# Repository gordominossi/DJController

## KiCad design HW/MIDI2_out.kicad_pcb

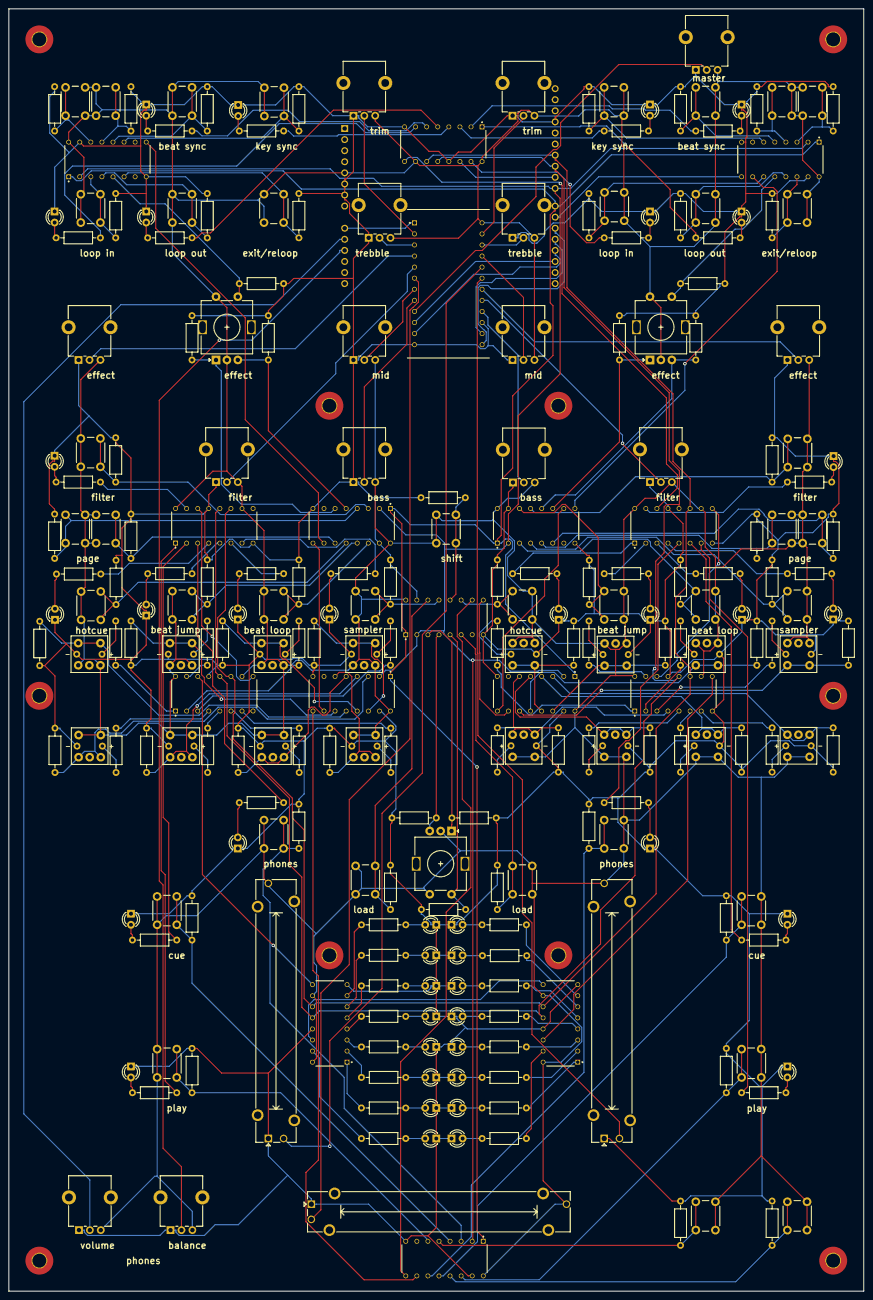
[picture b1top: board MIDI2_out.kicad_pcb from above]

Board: 2 copper layers, 196.0 x 294.0 mm, 263 parts (1 on the bottom side), 220 nets.

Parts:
A1: Arduino_UNO_R3
B0, B1, B2, B3, B4, B5, B6, B7: 74HC165; DIP794W45P254L1969H508Q16
D1, D2, D3, D4, D5, D6, D7, D8, D9, D10, D11, D12, D13, D14, D15, D16, D25, D26, D27, D28, D29, D30, D31, D32, D41, D42, D43, D44, D45, D46, D47, D48, D49, D50, D51, D52, D53, D54, D55, D56: LED; LED_D3.0mm
H0, H1, H2, H3, H4, H5, H6, H7, H8, H9: MountingHole_3.2mm_M3_Pad_TopBottom
L0, L1, L2, L3, L4, L5, L6: 74AHC595; DIP794W45P254L1969H508Q16
M0: CD74HC4067M; DIP1549W45P254L3404H940Q24
R1, R2, R3, R4, R5, R6, R7, R8, R9, R10, R11, R12, R13, R14, R15, R16, R17, R18, R19, R20, R21, R22, R23, R24, R25, R26, R27, R28, R29, R30, R31, R32, R33, R34, R35, R36, R37, R38, R39, R40, R41, R42, R43, R44, R45, R46, R47, R48, R49, R50, R51, R52, R53, R54, R55, R56: 220; R_Axial_DIN0207_L6.3mm_D2.5mm_P10.16mm_Horizontal
R57, R58, R59, R60, R61, R62, R63, R64, R65, R66, R67, R68, R69, R70, R71, R72, R89, R90, R91, R93, R95, R96, R97, R98, R100, R102, R103, R105, R107, R108, R109, R110, R111, R113, R115, R116, R118, R119, R121, R122, R123, R124, R125, R126, R127, R128, R129, R131, R133, R134, R135, R136, R138, R140, R141, R142, R143, R144, R145, R146, R148, R149, R151, R152: 10k; R_Axial_DIN0207_L6.3mm_D2.5mm_P10.16mm_Horizontal
RV1, RV2, RV3, RV4, RV5, RV6, RV10, RV11, RV12, RV13, RV14, RV15, RV16, RV17, RV18: 10k; Potentiometer_Alpha_RD901F-40-00D_Single_Vertical_CircularH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
RV7, RV8, RV9: 10k; Potentiometer_Bourns_PTA4543_Single_Slide
SW1, SW2, SW4, SW5, SW7, SW9, SW11, SW12, SW14, SW15, SW19, SW21, SW22, SW23, SW24, SW26, SW27, SW29, SW30, SW31, SW33, SW34, SW36, SW37, SW38, SW40, SW41, SW43, SW44, SW45, SW46, SW47, SW49, SW50, SW52, SW53, SW54, SW56, SW57: SW_Push; SW_PUSH_6mm_H13mm
SW3, SW6, SW10, SW13, SW17, SW20, SW25, SW28, SW32, SW35, SW39, SW42, SW48, SW51, SW55, SW58: SW_SPST_LED_2; TS5
SW8, SW16, SW18: Rotary_Encoder_Switch; RotaryEncoder_Alps_EC11E-Switch_Vertical_H20mm

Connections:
+5V: A1.5, B0.16, B1.16, B2.16, B3.16, B4.16, B5.16, B6.16, B7.16, L0.10, L0.16, L1.10, L1.16, L2.10, L2.16, L3.10, L3.16, L4.10, L4.16, L5.10, L5.16, L6.10, L6.16, M0.24, RV1.3, RV2.3, RV3.3, RV4.3, RV5.3, RV6.3, RV7.3, RV8.3, RV9.3, RV10.3, RV11.3, RV12.3, RV13.3, RV14.3, RV15.3, RV16.3, RV17.3, RV18.3, SW1.2, SW2.2, SW3.1, SW3.2, SW4.2, SW5.1, SW6.1, SW6.2, SW7.2, SW8.C, SW8.S1, SW9.2, SW10.1, SW10.2, SW11.2, SW12.1, SW13.1, SW13.2, SW14.2, SW15.2, SW16.C, SW16.S2, SW17.3, SW17.4, SW18.C, SW18.S2, SW19.1, SW20.3, SW20.4, SW21.2, SW22.2, SW23.2, SW24.2, SW25.3, SW25.4, SW26.2, SW27.1, SW28.3, SW28.4, SW29.2, SW30.2, SW31.2, SW32.1, SW32.2, SW33.1, SW34.1, SW35.1, SW35.2, SW36.1, SW37.2, SW38.2, SW39.1, SW39.2, SW40.1, SW41.1, SW42.1, SW42.2, SW43.2, SW44.2, SW45.2, SW46.2, SW47.2, SW48.3, SW48.4, SW49.1, SW50.1, SW51.3, SW51.4, SW52.2, SW53.1, SW54.2, SW55.3, SW55.4, SW56.1, SW57.1, SW58.3, SW58.4
GND: A1.6, A1.7, A1.29, B0.8, B0.15, B1.8, B1.15, B2.8, B2.15, B3.8, B3.15, B4.8, B4.15, B5.8, B5.15, B6.8, B6.15, B7.8, B7.15, D1.1, D2.1, D3.1, D4.1, D5.1, D6.1, D7.1, D8.1, D9.1, D10.1, D11.1, D12.1, D13.1, D14.1, D15.1, D16.1, D25.1, D26.1, D27.1, D28.1, D29.1, D30.1, D31.1, D32.1, D41.1, D42.1, D43.1, D44.1, D45.1, D46.1, D47.1, D48.1, D49.1, D50.1, D51.1, D52.1, D53.1, D54.1, D55.1, D56.1, L0.8, L0.13, L1.8, L1.13, L2.8, L2.13, L3.8, L3.13, L4.8, L4.13, L5.8, L5.13, L6.8, L6.13, M0.12, M0.15, R57.2, R58.2, R59.2, R60.2, R61.2, R62.2, R63.2, R64.2, R65.2, R66.2, R67.2, R68.2, R69.2, R70.2, R71.2, R72.2, R89.2, R90.2, R91.2, R93.2, R95.2, R96.2, R97.2, R98.2, R100.2, R102.2, R103.2, R105.2, R107.2, R108.2, R109.2, R110.2, R111.2, R113.2, R115.2, R116.2, R118.2, R119.2, R121.2, R122.2, R123.2, R124.2, R125.2, R126.2, R127.2, R128.2, R129.2, R131.2, R133.2, R134.2, R135.2, R136.2, R138.2, R140.2, R141.2, R142.2, R143.2, R144.2, R145.2, R146.2, R148.2, R149.2, R151.2, R152.2, RV1.1, RV2.1, RV3.1, RV4.1, RV5.1, RV6.1, RV7.1, RV8.1, RV9.1, RV10.1, RV11.1, RV12.1, RV13.1, RV14.1, RV15.1, RV16.1, RV17.1, RV18.1, SW3.5, SW6.5, SW10.5, SW13.5, SW17.5, SW20.5, SW25.5, SW28.5, SW32.5, SW35.5, SW39.5, SW42.5, SW48.5, SW51.5, SW55.5, SW58.5
unnamed: A1.9, M0.1
unnamed: A1.10, RV17.2
unnamed: A1.11, RV18.2
unnamed: A1.17, M0.10
unnamed: A1.18, M0.11
unnamed: A1.19, M0.14
unnamed: A1.20, M0.13
unnamed: A1.21, B0.9
unnamed: A1.22, B0.1, B1.1, B2.1, B3.1, B4.1, B5.1, B6.1, B7.1
unnamed: A1.23, B0.2, B1.2, B2.2, B3.2, B4.2, B5.2, B6.2, B7.2
unnamed: A1.24, L0.14
unnamed: A1.25, L0.12, L1.12, L2.12, L3.12, L4.12, L5.12, L6.12
unnamed: A1.26, L0.11, L1.11, L2.11, L3.11, L4.11, L5.11, L6.11
unnamed: B0.3, R109.1, SW9.1
unnamed: B0.4, R96.1, SW1.1
unnamed: B0.5, R140.1, SW38.1
unnamed: B0.6, R122.1, SW21.1
unnamed: B0.10, B1.9
unnamed: B0.11, R144.1, SW36.2
unnamed: B0.12, R116.1, SW16.S1
unnamed: B0.13, R136.1, SW37.1
unnamed: B0.14, R126.1, SW26.1
unnamed: B1.3, R110.1, SW11.1
unnamed: B1.4, R97.1, SW2.1
unnamed: B1.5, R143.1, SW44.1
unnamed: B1.6, R123.1, SW22.1
unnamed: B1.10, B2.9
unnamed: B1.11, R90.1, SW16.A
unnamed: B1.12, R89.1, SW16.B
unnamed: B1.13, R133.1, SW43.1
unnamed: B1.14, R127.1, SW29.1
unnamed: B2.3, R63.1, SW28.1, SW28.2
unnamed: B2.4, R61.1, SW25.1, SW25.2
unnamed: B2.5, R59.1, SW20.1, SW20.2
unnamed: B2.6, R57.1, SW17.1, SW17.2
unnamed: B2.10, B3.9
unnamed: B2.11, R71.1, SW13.3, SW13.4
unnamed: B2.12, R69.1, SW10.3, SW10.4
unnamed: B2.13, R67.1, SW6.3, SW6.4
unnamed: B2.14, R65.1, SW3.3, SW3.4
unnamed: B3.3, R107.1, SW8.A
unnamed: B3.4, R103.1, SW8.B
unnamed: B3.5, R91.1, SW8.S2
unnamed: B3.6, R148.1, SW54.1
unnamed: B3.10, B4.9
unnamed: B3.11, R135.1, SW56.2
unnamed: B3.12, R134.1, SW49.2
unnamed: B3.13, R128.1, SW40.2
unnamed: B3.14, R118.1, SW33.2
unnamed: B4.3, R113.1, SW27.2
unnamed: B4.4, R105.1, SW19.2
unnamed: B4.5, R100.1, SW12.2
unnamed: B4.6, R93.1, SW5.2
unnamed: B4.10, B5.9
unnamed: B4.11, R149.1, SW57.2
unnamed: B4.12, R138.1, SW50.2
unnamed: B4.13, R131.1, SW41.2
unnamed: B4.14, R119.1, SW34.2
unnamed: B5.3, R64.1, SW48.1, SW48.2
unnamed: B5.4, R62.1, SW51.1, SW51.2
unnamed: B5.5, R60.1, SW55.1, SW55.2
unnamed: B5.6, R58.1, SW58.1, SW58.2
unnamed: B5.10, B6.9
unnamed: B5.11, R72.1, SW32.3, SW32.4
unnamed: B5.12, R70.1, SW35.3, SW35.4
unnamed: B5.13, R68.1, SW39.3, SW39.4
unnamed: B5.14, R66.1, SW42.3, SW42.4
unnamed: B6.3, R129.1, SW30.1
unnamed: B6.4, R141.1, SW46.1
unnamed: B6.5, R102.1, SW18.B
unnamed: B6.6, R115.1, SW18.A
unnamed: B6.10, B7.9
unnamed: B6.11, R124.1, SW23.1
unnamed: B6.12, R145.1, SW45.1
unnamed: B6.13, R95.1, SW4.1
unnamed: B6.14, R108.1, SW14.1
unnamed: B7.3, R125.1, SW31.1
unnamed: B7.4, R151.1, SW52.1
unnamed: B7.5, R146.1, SW18.S1
unnamed: B7.6, R142.1, SW53.2
unnamed: B7.11, R121.1, SW24.1
unnamed: B7.12, R152.1, SW47.1
unnamed: B7.13, R98.1, SW7.1
unnamed: B7.14, R111.1, SW15.1
unnamed: D1.2, R1.1
unnamed: D2.2, R2.1
unnamed: D3.2, R3.1
unnamed: D4.2, R4.1
unnamed: D5.2, R5.1
unnamed: D6.2, R6.1
unnamed: D7.2, R7.1
unnamed: D8.2, R8.1
unnamed: D9.2, R25.1
unnamed: D10.2, R26.1
unnamed: D11.2, R27.1
unnamed: D12.2, R28.1
unnamed: D13.2, R29.1
unnamed: D14.2, R30.1
unnamed: D15.2, R31.1
unnamed: D16.2, R32.1
unnamed: D25.2, R41.2
unnamed: D26.2, R42.2
unnamed: D27.2, R43.2
unnamed: D28.2, R44.2
unnamed: D29.2, R45.2
unnamed: D30.2, R46.2
unnamed: D31.2, R47.2
unnamed: D32.2, R48.2
unnamed: D41.2, R9.2
unnamed: D42.2, R10.2
unnamed: D43.2, R11.2
unnamed: D44.2, R12.2
unnamed: D45.2, R13.2
unnamed: D46.2, R14.2
unnamed: D47.2, R15.2
unnamed: D48.2, R16.2
unnamed: D49.2, R17.2
unnamed: D50.2, R18.2
unnamed: D51.2, R19.2
unnamed: D52.2, R20.2
unnamed: D53.2, R21.2
unnamed: D54.2, R22.2
unnamed: D55.2, R23.2
unnamed: D56.2, R24.2
unnamed: L0.1, R26.2
unnamed: L0.2, R27.2
unnamed: L0.3, R28.2
unnamed: L0.4, R29.2
unnamed: L0.5, R30.2
unnamed: L0.6, R31.2
unnamed: L0.7, R32.2
unnamed: L0.9, L1.14
unnamed: L0.15, R25.2
unnamed: L1.1, R42.1
unnamed: L1.2, R43.1
unnamed: L1.3, R44.1
unnamed: L1.4, R45.1
unnamed: L1.5, R46.1
unnamed: L1.6, R47.1
unnamed: L1.7, R48.1
unnamed: L1.9, L2.14
unnamed: L1.15, R41.1
unnamed: L2.1, R34.2
unnamed: L2.2, R35.2
unnamed: L2.3, R36.2
unnamed: L2.4, R37.2
unnamed: L2.5, R38.2
unnamed: L2.6, R39.2
unnamed: L2.7, R40.2
unnamed: L2.9, L3.14
unnamed: L2.15, R33.2
unnamed: L3.1, R2.2
unnamed: L3.2, R3.2
unnamed: L3.3, R4.2
unnamed: L3.4, R5.2
unnamed: L3.5, R6.2
unnamed: L3.6, R7.2
unnamed: L3.7, R8.2
unnamed: L3.9, L4.14
unnamed: L3.15, R1.2
unnamed: L4.1, R18.1
unnamed: L4.2, R19.1
unnamed: L4.3, R20.1
unnamed: L4.4, R21.1
unnamed: L4.5, R22.1
unnamed: L4.6, R23.1
unnamed: L4.7, R24.1
unnamed: L4.9, L5.14
unnamed: L4.15, R17.1
unnamed: L5.1, R50.2
unnamed: L5.2, R51.2
unnamed: L5.3, R52.2
unnamed: L5.4, R53.2
unnamed: L5.5, R54.2
unnamed: L5.6, R55.2
unnamed: L5.7, R56.2
unnamed: L5.9, L6.14
unnamed: L5.15, R49.2
unnamed: L6.1, R10.1
unnamed: L6.2, R11.1
unnamed: L6.3, R12.1
unnamed: L6.4, R13.1
unnamed: L6.5, R14.1
unnamed: L6.6, R15.1
unnamed: L6.7, R16.1
unnamed: L6.15, R9.1
unnamed: M0.2, RV16.2
unnamed: M0.3, RV14.2
unnamed: M0.4, RV12.2
unnamed: M0.5, RV10.2
unnamed: M0.6, RV8.2
unnamed: M0.7, RV6.2
unnamed: M0.8, RV4.2
unnamed: M0.9, RV2.2
unnamed: M0.16, RV1.2
unnamed: M0.17, RV3.2
unnamed: M0.18, RV5.2
unnamed: M0.19, RV7.2
unnamed: M0.20, RV9.2
unnamed: M0.21, RV11.2
unnamed: M0.22, RV13.2
unnamed: M0.23, RV15.2
unnamed: R33.1, SW3.6
unnamed: R34.1, SW6.6
unnamed: R35.1, SW10.6
unnamed: R36.1, SW13.6
unnamed: R37.1, SW17.6
unnamed: R38.1, SW20.6
unnamed: R39.1, SW25.6
unnamed: R40.1, SW28.6
unnamed: R49.1, SW32.6
unnamed: R50.1, SW35.6
unnamed: R51.1, SW39.6
unnamed: R52.1, SW42.6
unnamed: R53.1, SW48.6
unnamed: R54.1, SW51.6
unnamed: R55.1, SW55.6
unnamed: R56.1, SW58.6

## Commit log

2021-08-09 Adding firmware
2021-08-09 Adding hardware Restructuring directories to accomodate hardware
2021-08-09 Formatting code Wrapping lines and removing trailling whitespaces
2022-03-19 Adding descriptive comments to the firmware Relocating hardware related definitions
